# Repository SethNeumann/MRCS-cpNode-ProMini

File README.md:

# MRCS-cpNode-ProMini
## License: Creative Commons Attribution-NonCommercial-ShareAlike

Arduino ProMini based CMRI node in 2.71" form

cpNode with a ProMini instead of a BBLeo

cpNode and I/O expander (IOX) boards have been updated to version
3.0. The Original BareBones BBLeo is EOL and Unavailable, so this respin is done
with a ProMini, which does not provide an independent USB serial interface.

  * Rev 3.0 boards are NOT backward compatible with previous versions. Software changes ARE needed.

What does a cpNode do?

cpNodes provide input and output (I/O) ports which connect to LEDs
for signals, push buttons, turnout motors, block detectors, and
other devices to a central computer for controlling model railroads.
cpNodes may also be used as standalone controllers for staging,
crossings and interlocking plants.

A cpNode has:

  * 16 I/O lines with solder pads for LED limiting resistors
  * Screw terminal blocks or solder pads to connect external devices - see configurations below
  * CMRInet RS-422/485 Network Interface.  CMRInet is now NMRA Layout Control Specification S9-10
  * I2C interface for adding Input/Output Expander (IOX) boards for more i/o ports
  * All the i/o needed to control one end of a CTC siding, just add signals and detectors and switch motor drivers
  * Female headers to receive a BB-Leo (Arduino) processor available from Modern Device, use coupon code "cpnode" or order the cpNode LE option
  * I/O is configured in 8 bit groups, providing up to 144 lines when fully expanded with IOX16s and/or IOX32s
  * Use cpNodes as small, economical, CMRI nodes as is or customize the code to support applications requiring local intelligence
  * Standard "Sketch" (Arduino program) is compatible with JMRI or traditional CMRI BASIC/Visual Basic development tools

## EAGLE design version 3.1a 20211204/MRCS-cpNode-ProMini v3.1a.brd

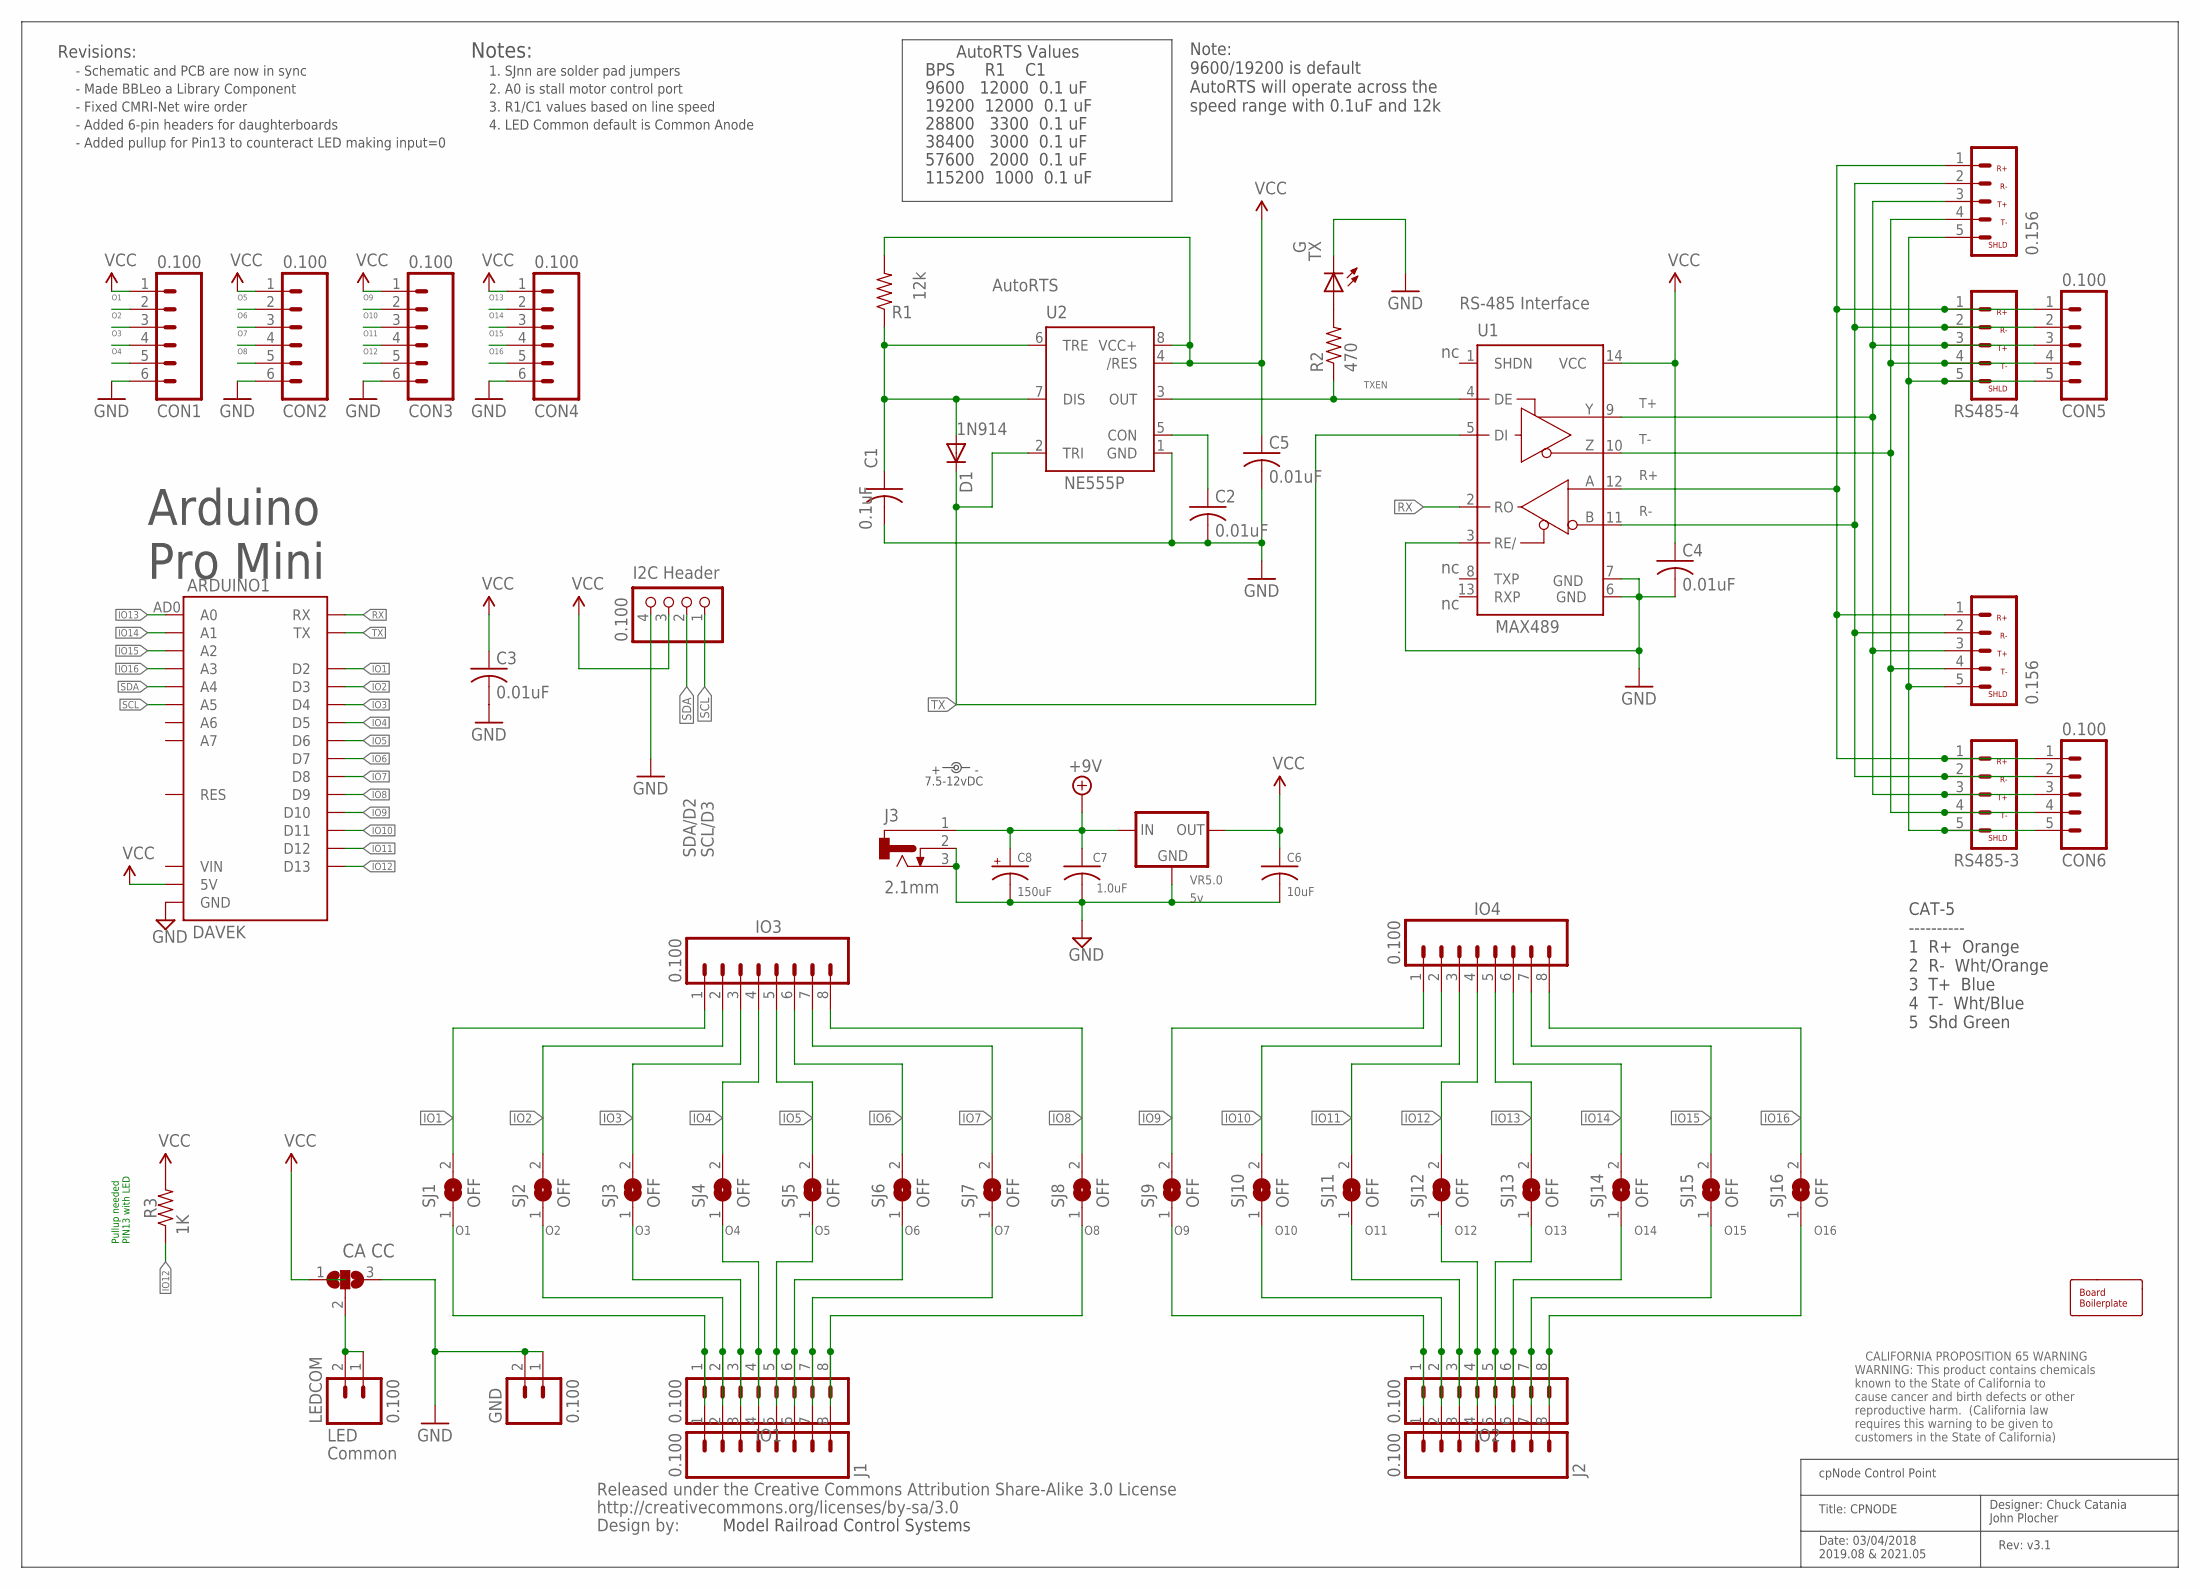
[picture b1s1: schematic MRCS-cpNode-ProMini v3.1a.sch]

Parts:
ARDUINO1: DAVEK; ARDUINO_PRO_MINI_DAVEK
BOARD1: BOARD; BOARD-DINRAIL-2.71IN-MRCS
C1: 0.1uF; C-PTH-0.100
C2, C3, C4, C5: 0.01uF; C-PTH-0.100
C6: 10uF; C050-024X044
C7: 1.0uF; C050-024X044
C8: 150uF; E5-10.5
CON1, CON2, CON3, CON4: 0.100; 1X06-SIP_LOCK
CON5, CON6: 0.100; 1X05_LOCK
D1: 1N4148; DIODE-1N4148
GND: 0.100; MOLEX-1X2_LOCK
I2CHDR: 0.100; 1X04/90
IO1, IO2, IO3, IO4: 0.100; 1X08
J1, J2: 0.100; 1X08_LOCK_LONGPADS
J3: 2.1mm; DCJ0202
LABEL1: 7.5-12vDC; PWR_LABEL
LEDCOM: 0.100; MOLEX-1X2_LOCK
P1: CA CC; 3P-SMD-2X4.8
R1: 12k; AXIAL-0.4-RES
R2: 470; AXIAL-0.4-RES
R3: 1K; AXIAL-0.4-RES
RS485-1, RS485-2: 0.156; KK-156-5
RS485-3, RS485-4: 3.5mm; CMRINET-3.5MM
SJ1, SJ2, SJ3, SJ4, SJ5, SJ6, SJ7, SJ8, SJ9, SJ10, SJ11, SJ12, SJ13, SJ14, SJ15, SJ16: OFF; SJ
TX: G; LED3MM
U1: MAX3465CPD; DIL14
U2: NE555P; DIL-08
U$1: CREATIVE_COMMONS
U$2: Prop65; CA-PROP65WARNING
VR5.0: 5v; TO-220-RA

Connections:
+9V: C7.1, C8.+, J3.1, VR5.0.IN
GND: ARDUINO1.GND@1 (GND), ARDUINO1.GND@2 (GND), ARDUINO1.GND@4 (GND), C1.2, C2.2, C3.2, C4.2, C5.2, C6.2, C7.2, C8.-, CON1.6, CON2.6, CON3.6, CON4.6, GND.1, GND.2, I2CHDR.4, J3.2, J3.3, P1.3, TX.K (C), U1.3 (RE/), U1.6 (GND), U1.7 (GND), U2.1 (GND), VR5.0.GND
IO1: ARDUINO1.D2, IO3.1, SJ1.2
IO2: ARDUINO1.D3, IO3.2, SJ2.2
IO3: ARDUINO1.D4, IO3.3, SJ3.2
IO4: ARDUINO1.D5, IO3.4, SJ4.2
IO5: ARDUINO1.D6, IO3.5, SJ5.2
IO6: ARDUINO1.D7, IO3.6, SJ6.2
IO7: ARDUINO1.D8, IO3.7, SJ7.2
IO8: ARDUINO1.D9, IO3.8, SJ8.2
IO9: ARDUINO1.D10, IO4.1, SJ9.2
IO10: ARDUINO1.D11, IO4.2, SJ10.2
IO11: ARDUINO1.D12, IO4.3, SJ11.2
IO12: ARDUINO1.D13, IO4.4, R3.P$1 (1), SJ12.2
IO13: ARDUINO1.AD0 (A0), IO4.5, SJ13.2
IO14: ARDUINO1.AD1 (A1), IO4.6, SJ14.2
IO15: ARDUINO1.AD2 (A2), IO4.7, SJ15.2
IO16: ARDUINO1.AD3 (A3), IO4.8, SJ16.2
unnamed: R2.P$2 (2), TX.A
unnamed: C2.1, U2.5 (CON)
unnamed: LEDCOM.1, LEDCOM.2, P1.2
unnamed: C1.1, D1.A, R1.P$1 (1), U2.6 (TRE), U2.7 (DIS)
O1: CON1.2, IO1.1, J1.1, SJ1.1
O2: CON1.3, IO1.2, J1.2, SJ2.1
O3: CON1.4, IO1.3, J1.3, SJ3.1
O4: CON1.5, IO1.4, J1.4, SJ4.1
O5: CON2.2, IO1.5, J1.5, SJ5.1
O6: CON2.3, IO1.6, J1.6, SJ6.1
O7: CON2.4, IO1.7, J1.7, SJ7.1
O8: CON2.5, IO1.8, J1.8, SJ8.1
O9: CON3.2, IO2.1, J2.1, SJ9.1
O10: CON3.3, IO2.2, J2.2, SJ10.1
O11: CON3.4, IO2.3, J2.3, SJ11.1
O12: CON3.5, IO2.4, J2.4, SJ12.1
O13: CON4.2, IO2.5, J2.5, SJ13.1
O14: CON4.3, IO2.6, J2.6, SJ14.1
O15: CON4.4, IO2.7, J2.7, SJ15.1
O16: CON4.5, IO2.8, J2.8, SJ16.1
R+: CON5.1, CON6.1, RS485-1.1, RS485-2.1, RS485-3.1, RS485-4.1, U1.12 (A)
R-: CON5.2, CON6.2, RS485-1.2, RS485-2.2, RS485-3.2, RS485-4.2, U1.11 (B)
RX: ARDUINO1.RX, U1.2 (RO)
SCL: ARDUINO1.AD5 (A5), I2CHDR.1
SDA: ARDUINO1.AD4 (A4), I2CHDR.2
SHIELD: CON5.5, CON6.5, RS485-1.5, RS485-2.5, RS485-3.5, RS485-4.5
T+: CON5.3, CON6.3, RS485-1.3, RS485-2.3, RS485-3.3, RS485-4.3, U1.9 (Y)
T-: CON5.4, CON6.4, RS485-1.4, RS485-2.4, RS485-3.4, RS485-4.4, U1.10 (Z)
TX: ARDUINO1.TX@1 (TX), D1.C, U1.5 (DI), U2.2 (TRI)
TXEN: R2.P$1 (1), U1.4 (DE), U2.3 (OUT)
VCC: ARDUINO1.5V, C3.1, C4.1, C5.1, C6.1, CON1.1, CON2.1, CON3.1, CON4.1, I2CHDR.3, P1.1, R1.P$2 (2), R3.P$2 (2), U1.14 (VCC), U2.4 (/RES), U2.8 (VCC+), VR5.0.OUT

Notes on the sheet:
Rev: v3.1
Date: 03/04/2018 2019.08 & 2021.05
Title: CPNODE
cpNode Control Point
Designer: Chuck Catania John Plocher
SDA/D2
SCL/D3
LED
1N914
MAX489
RS-485 Interface
Notes:
1. SJnn are solder pad jumpers
2. A0 is stall motor control port
I2C Header
3. R1/C1 values based on line speed
AutoRTS
AutoRTS Values
9600 12000 0.1 uF
19200 12000 0.1 uF
38400 3000 0.1 uF
57600 2000 0.1 uF
115200 1000 0.1 uF
BPS R1 C1
Common
4. LED Common default is Common Anode
Model Railroad Control Systems
Revisions:
CAT-5 ---------- 1 R+ Orange 2 R- Wht/Orange 3 T+ Blue 4 T- Wht/Blue 5 Shd Green
28800 3300 0.1 uF
Note: 9600/19200 is default AutoRTS will operate across the speed range with 0.1uF and 12k
- Fixed CMRI-Net wire order
- Schematic and PCB are now in sync
- Made BBLeo a Library Component
- Added 6-pin headers for daughterboards
Arduino Pro Mini
Pullup needed PIN13 with LED
- Added pullup for Pin13 to counteract LED making input=0

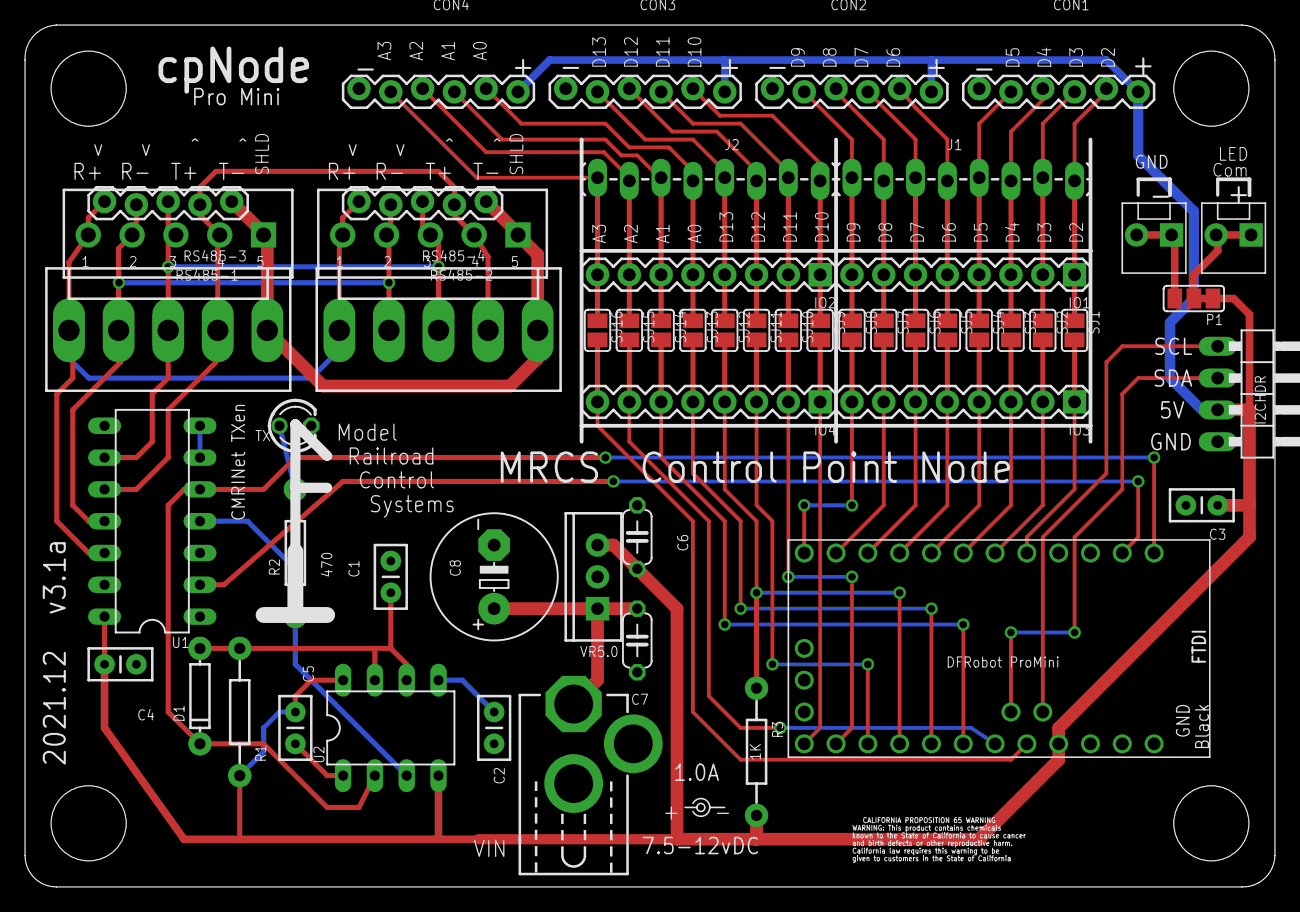
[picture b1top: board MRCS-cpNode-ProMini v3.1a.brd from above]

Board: 2 copper layers, 99.8 x 68.8 mm, 59 parts (0 on the bottom side), 49 nets.

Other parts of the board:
U$3: MRCS; MRCS-LOGO

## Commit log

2020-12-09 Initial version
2021-06-03 add pullup to pin13
2021-06-30 larger mounting holes
2021-06-30 fixed license notes
2021-12-04 changed value of pull down to 1K, moved Auto RTS resistor
    The best value or the pull down on D13 (R1) is 1K, not 2.2K, mask adjusted. Moved the autoRTS resistor (R2) so it's easier to change.
2021-12-04 clean up for 3.1a
    moving files around in the source directory
2022-06-24 Create cpNode Promini BOM.pdf
    MRCS-cpNode-ProMini Bill of Materials
2023-05-07 Basic Assembly instructions
    Assembly instructions

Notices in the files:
parts and their libraries:
SparkFun: Released under the Creative Commons Attribution Share-Alike 3.0 License
SparkFun: http://creativecommons.org/licenses/by-sa/3.0
